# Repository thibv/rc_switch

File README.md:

# rc_switch
Control a transistor with a channel of an RC receiver

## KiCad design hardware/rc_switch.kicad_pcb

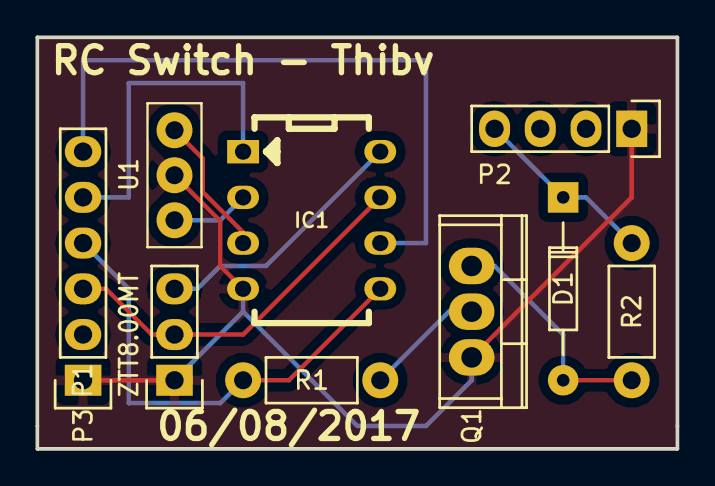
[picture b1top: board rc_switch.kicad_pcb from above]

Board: 2 copper layers, 35.6 x 22.9 mm, 9 parts (0 on the bottom side), 11 nets.

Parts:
D1: 1N4148; Diode_DO-35_SOD27_Horizontal_RM10
IC1: ATTINY85-P; DIP-8
P1: CONN_01X03; Socket_Strip_Straight_1x03
P2: CONN_01X04; Socket_Strip_Straight_1x04
P3: CONN_02X03; Socket_Strip_Straight_1x06
Q1: BUZ11; TO-220
R1: 0; Resistor_Horizontal_RM7mm
R2: LOAD; Resistor_Horizontal_RM7mm
U1: ZTT8.00MT

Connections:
+5V: IC1.8, P1.3
/CELL3: D1.1, P2.4, R2.2
/CMD: IC1.5, P3.4, R1.2
/MISO: IC1.6, P3.6
/RECEIVER: IC1.7, P1.2, P3.3
/RST: IC1.1, P3.5
GND: IC1.4, P1.1, P2.1, P3.1, Q1.3, U1.2
unnamed: D1.2, Q1.1, R2.1
unnamed: IC1.2, U1.1
unnamed: IC1.3, U1.3
unnamed: Q1.2, R1.1

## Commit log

2017-08-06 RC Switch : Initial commit Control a transistor with a channel of an RC receiver
2017-08-16 Removing some components to keep only the strictly necessary parts. Adding mounting holes.
